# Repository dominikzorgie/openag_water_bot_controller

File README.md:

# OpenAg Waterbot Controller
Printed Circuit Board (PCB) that enables computer control for nutrient dosing in the Food Server (FS)

## Contents
- [Specification](documentation/spec.md) - High level description of the system.
- Bill of Materials
  - [PCB BOM](documentation/pcb_bom.csv) - all components required to assemble the PCB only. Includes microcontrollers, diodes, relays, resistors, etc.
  - [Enclosure BOM](documentation/enclosure_bom.csv) - All components required to assemble the encolsure around the PCB. Includes encapsulation shell, connectors, wire, potting, etc.
  - [Wiring Harness BOM](documentation/wiring_harness_bom.csv) - All components required to assemble the wiring harnesses for connecting the waterbot controller to the solenoids and brain box. Includes connectors, wires, heat shrink, etc.
  - [Tool BOM](documentation/tool_bom.csv) - All tools required to fabricate the enclosure and wire harnesses. Includes potting dispenser gun, powerpole crimper, etc.

## System Block Diagram

## Connection Diagram

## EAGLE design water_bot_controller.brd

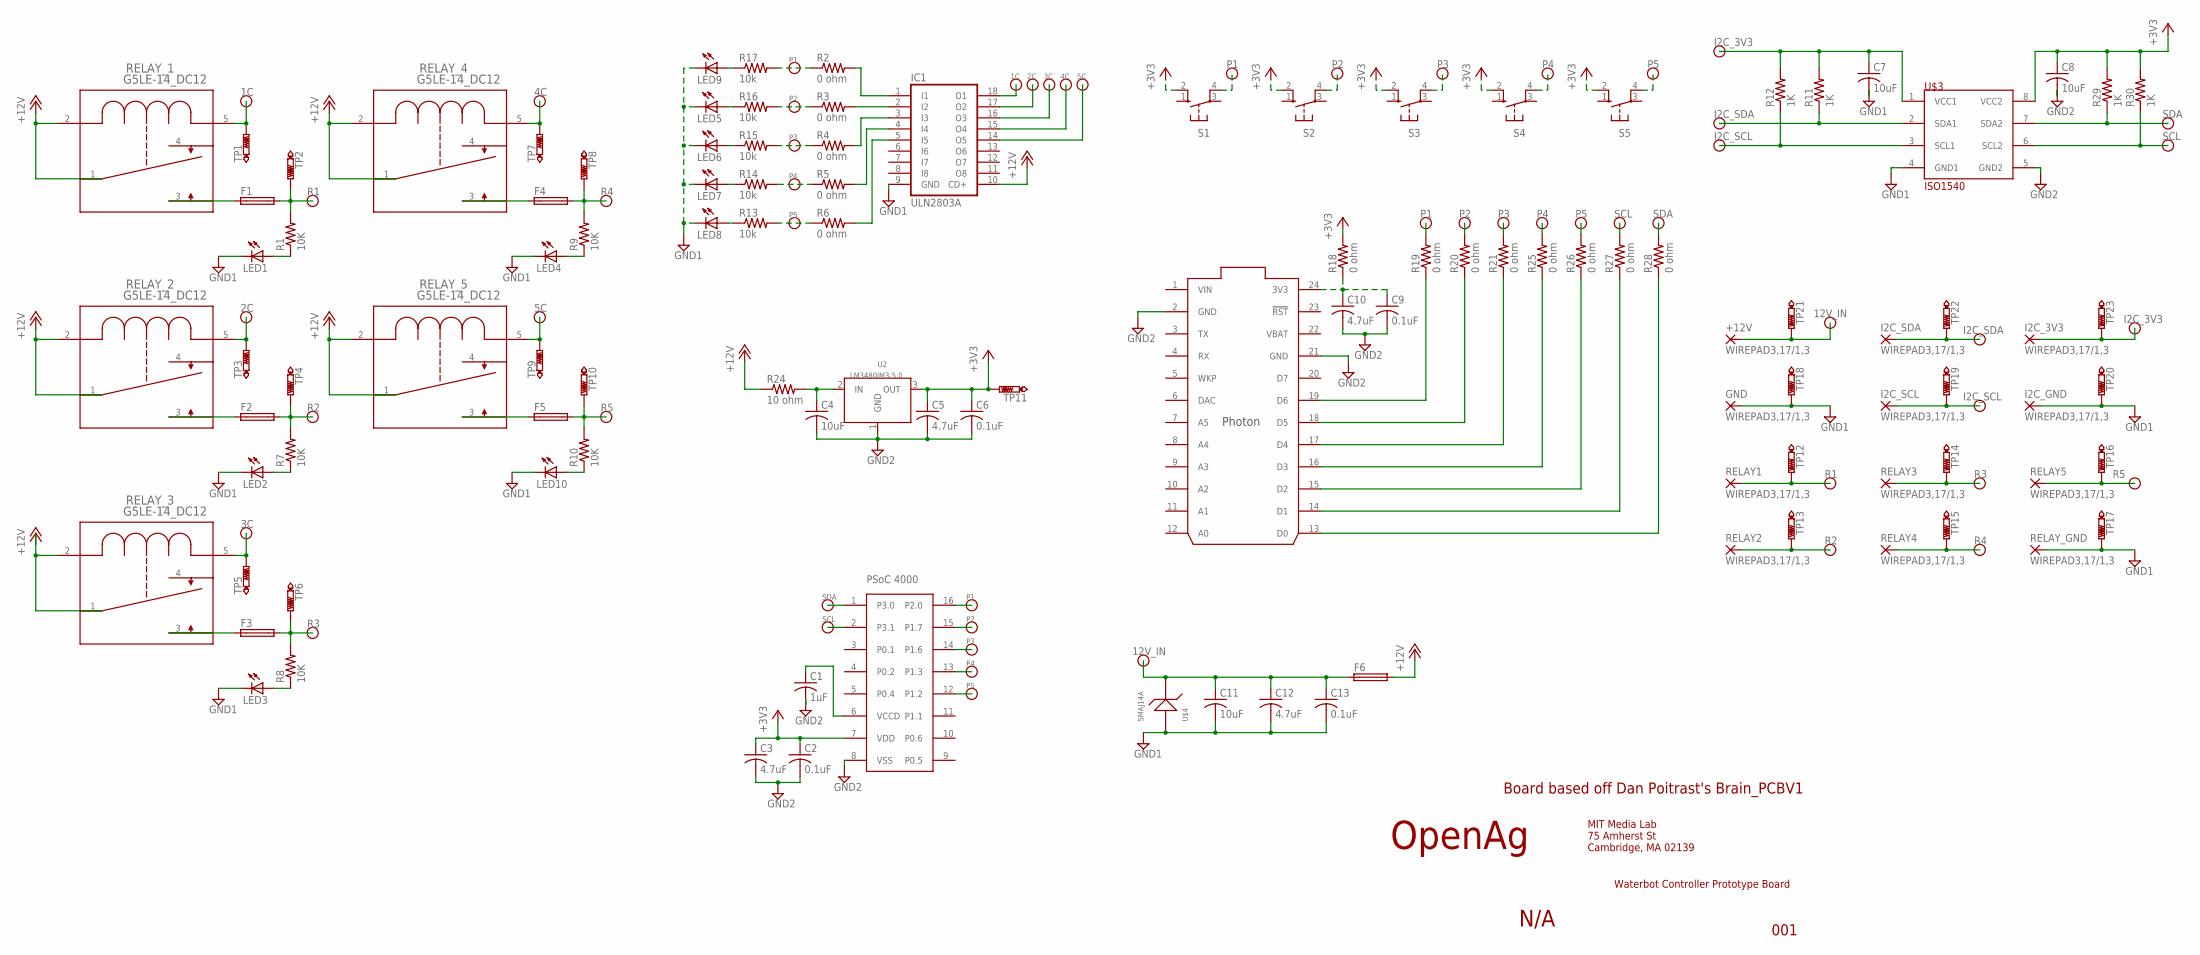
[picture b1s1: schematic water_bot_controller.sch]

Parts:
+12V: WIREPAD3,17/1,3; 3,17/1,3
C1: 1uF; C0603
C2, C6, C9, C13: 0.1uF; C0603
C3, C5, C10, C12: 4.7uF; C1206
C4, C7, C8, C11: 10uF; C1206
F1, F2, F3, F4, F5, F6: GSH15
GND: WIREPAD3,17/1,3; 3,17/1,3
I2C_3V3, I2C_GND, I2C_SCL, I2C_SDA: WIREPAD3,17/1,3; 3,17/1,3
IC1: ULN2803A; DIL18
LED1, LED2, LED3, LED4, LED5, LED6, LED7, LED8, LED10: LEDCHIP-LED0603; CHIP-LED0603
LED9: LED; SMARTLED-TTW
R1, R7, R8, R9, R10: 10K; R0603
R2, R3, R4, R5, R6, R18, R19, R20, R21, R25, R26, R27, R28: 0 ohm; R0603
R11, R12, R29, R30: 1K; R0603
R13, R14, R15, R16, R17: 10k; R0603
R24: 10 ohm; R0603
RELAY1, RELAY2, RELAY3, RELAY4, RELAY5: WIREPAD3,17/1,3; 3,17/1,3
RELAY_1, RELAY_2, RELAY_3, RELAY_4, RELAY_5: G5LE-14_DC12; RELAY_G5LE-1
RELAY_GND: WIREPAD3,17/1,3; 3,17/1,3
S1, S2, S3, S4, S5: 10-XX; B3F-10XX
TP1, TP2, TP3, TP4, TP5, TP6, TP7, TP8, TP9, TP10, TP11, TP12, TP13, TP14, TP15, TP16, TP17, TP18, TP19, TP20, TP21, TP22, TP23: PTR1B2,54; B2,54
U2: LM3480IM3-5.0; SOT-23
U$1: PSOC_4000; SOIC16
U$2: PHOTON_WITH_HEADERS; PHOTON
U$3: ISO1540; SOIC8
U$4: SMAJ14A; DO-214AC

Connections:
1C: IC1.18 (O1), RELAY_1.5, TP1.TP
2C: IC1.17 (O2), RELAY_2.5, TP3.TP
3C: IC1.16 (O3), RELAY_3.5, TP5.TP
4C: IC1.15 (O4), RELAY_4.5, TP7.TP
5C: IC1.14 (O5), RELAY_5.5, TP9.TP
12V_IN: +12V.1, C11.1, C12.1, C13.1, F6.1, TP21.TP, U$4.C
+3V3: C2.1, C3.1, C5.1, C6.1, C8.1, R18.2, R29.2, R30.2, S1.2 (S1), S2.2 (S1), S3.2 (S1), S4.2 (S1), S5.2 (S1), TP11.TP, U2.3 (OUT), U$1.7 (VDD), U$3.8 (VCC2)
+12V: F6.2, IC1.10 (CD+), R24.1, RELAY_1.1 (2), RELAY_1.2 (1), RELAY_2.1 (2), RELAY_2.2 (1), RELAY_3.1 (2), RELAY_3.2 (1), RELAY_4.1 (2), RELAY_4.2 (1), RELAY_5.1 (2), RELAY_5.2 (1)
GND1: C7.2, C11.2, C12.2, C13.2, GND.1, I2C_GND.1, IC1.9 (GND), LED1.C, LED2.C, LED3.C, LED4.C, LED5.C, LED6.C, LED7.C, LED8.C, LED9.C@1 (C), LED10.C, RELAY_GND.1, TP17.TP, TP18.TP, TP20.TP, U$3.4 (GND1), U$4.A
GND2: C1.2, C2.2, C3.2, C4.2, C5.2, C6.2, C8.2, C9.2, C10.2, U2.1 (GND), U$1.8 (VSS), U$2.2 (GND), U$2.21 (GND), U$3.5 (GND2)
I2C_3V3: C7.1, I2C_3V3.1, R11.2, R12.2, TP23.TP, U$3.1 (VCC1)
I2C_SCL: I2C_SCL.1, R12.1, TP19.TP, U$3.3 (SCL1)
I2C_SDA: I2C_SDA.1, R11.1, TP22.TP, U$3.2 (SDA1)
unnamed: LED1.A, R1.1
unnamed: F1.1, RELAY_1.3
unnamed: F2.1, RELAY_2.3
unnamed: LED2.A, R7.1
unnamed: IC1.1 (I1), R2.2
unnamed: IC1.3 (I3), R4.2
unnamed: IC1.5 (I5), R6.2
unnamed: IC1.4 (I4), R5.2
unnamed: F3.1, RELAY_3.3
unnamed: LED3.A, R8.1
unnamed: F4.1, RELAY_4.3
unnamed: LED9.A@1 (A), R17.1
unnamed: LED5.A, R16.1
unnamed: LED6.A, R15.1
unnamed: LED7.A, R14.1
unnamed: LED8.A, R13.1
unnamed: LED4.A, R9.1
unnamed: F5.1, RELAY_5.3
unnamed: LED10.A, R10.1
unnamed: R26.1, U$2.15 (D2)
unnamed: R27.1, U$2.14 (D1)
unnamed: C9.1, C10.1, R18.1, U$2.24 (3V3)
unnamed: R19.1, U$2.19 (D6)
unnamed: R20.1, U$2.18 (D5)
unnamed: R21.1, U$2.17 (D4)
unnamed: R25.1, U$2.16 (D3)
unnamed: R28.1, U$2.13 (D0)
unnamed: C1.1, U$1.6 (VCCD)
unnamed: C4.1, R24.2, U2.2 (IN)
P1: R2.1, R17.2, R19.2, S1.4 (P1), U$1.16 (P2.0)
P2: R3.1, R16.2, R20.2, S2.4 (P1), U$1.15 (P1.7)
P3: R4.1, R15.2, R21.2, S3.4 (P1), U$1.14 (P1.6)
P4: R5.1, R14.2, R25.2, S4.4 (P1), U$1.13 (P1.3)
P5: R6.1, R13.2, R26.2, S5.4 (P1), U$1.12 (P1.2)
R1: F1.2, R1.2, RELAY1.1, TP2.TP, TP12.TP
R2: F2.2, R7.2, RELAY2.1, TP4.TP, TP13.TP
R3: F3.2, R8.2, RELAY3.1, TP6.TP, TP14.TP
R4: F4.2, R9.2, RELAY4.1, TP8.TP, TP15.TP
R5: F5.2, R10.2, RELAY5.1, TP10.TP, TP16.TP
SCL: R27.2, R30.1, U$1.2 (P3.1), U$3.6 (SCL2)
SDA: R28.2, R29.1, U$1.1 (P3.0), U$3.7 (SDA2)
VBAT: U$2.22 (VBAT)
VIN: U$2.1 (VIN)

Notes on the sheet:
Waterbot Controller Prototype Board
OpenAg
MIT Media Lab 75 Amherst St Cambridge, MA 02139
N/A
001
Board based off Dan Poitrast's Brain_PCBV1
LM3480IM3-5.0

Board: 2 copper layers, 108 parts (0 on the bottom side), 54 nets, no tracks yet.

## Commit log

2017-09-05 added initial spec
2017-09-05 added relay circuitry
2017-09-19 added microcontroller module, cleaned up relay driver module
2017-10-02 cleaned up relay module
2017-10-02 added connection diagram option
2017-10-02 restructured files
2017-10-03 spec'd pwr/sig conns, added pushbuttons to schematic
2017-10-03 added optional particle photon headers
2017-10-04 added i2c isolation circuitry, replaced leds, and added test points
2017-10-04 added 12v power conditioning
